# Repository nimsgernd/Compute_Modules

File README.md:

# Compute_Modules
I would like to design some compute modules for several processors that I would like more experience designing for. Not something I will be able to work on now but eventually.

Processors to support:
|   | Processor Name              |
| - | --------------------------- |
| 1 | AMD Xilinx Zynq UltraScale+ |
| 2 | AMD V2000                   |
| 3 | RP2350                      |
| 4 | STM32G491RET6               |
| 5 | STM32H75XXXXX - TBD         |

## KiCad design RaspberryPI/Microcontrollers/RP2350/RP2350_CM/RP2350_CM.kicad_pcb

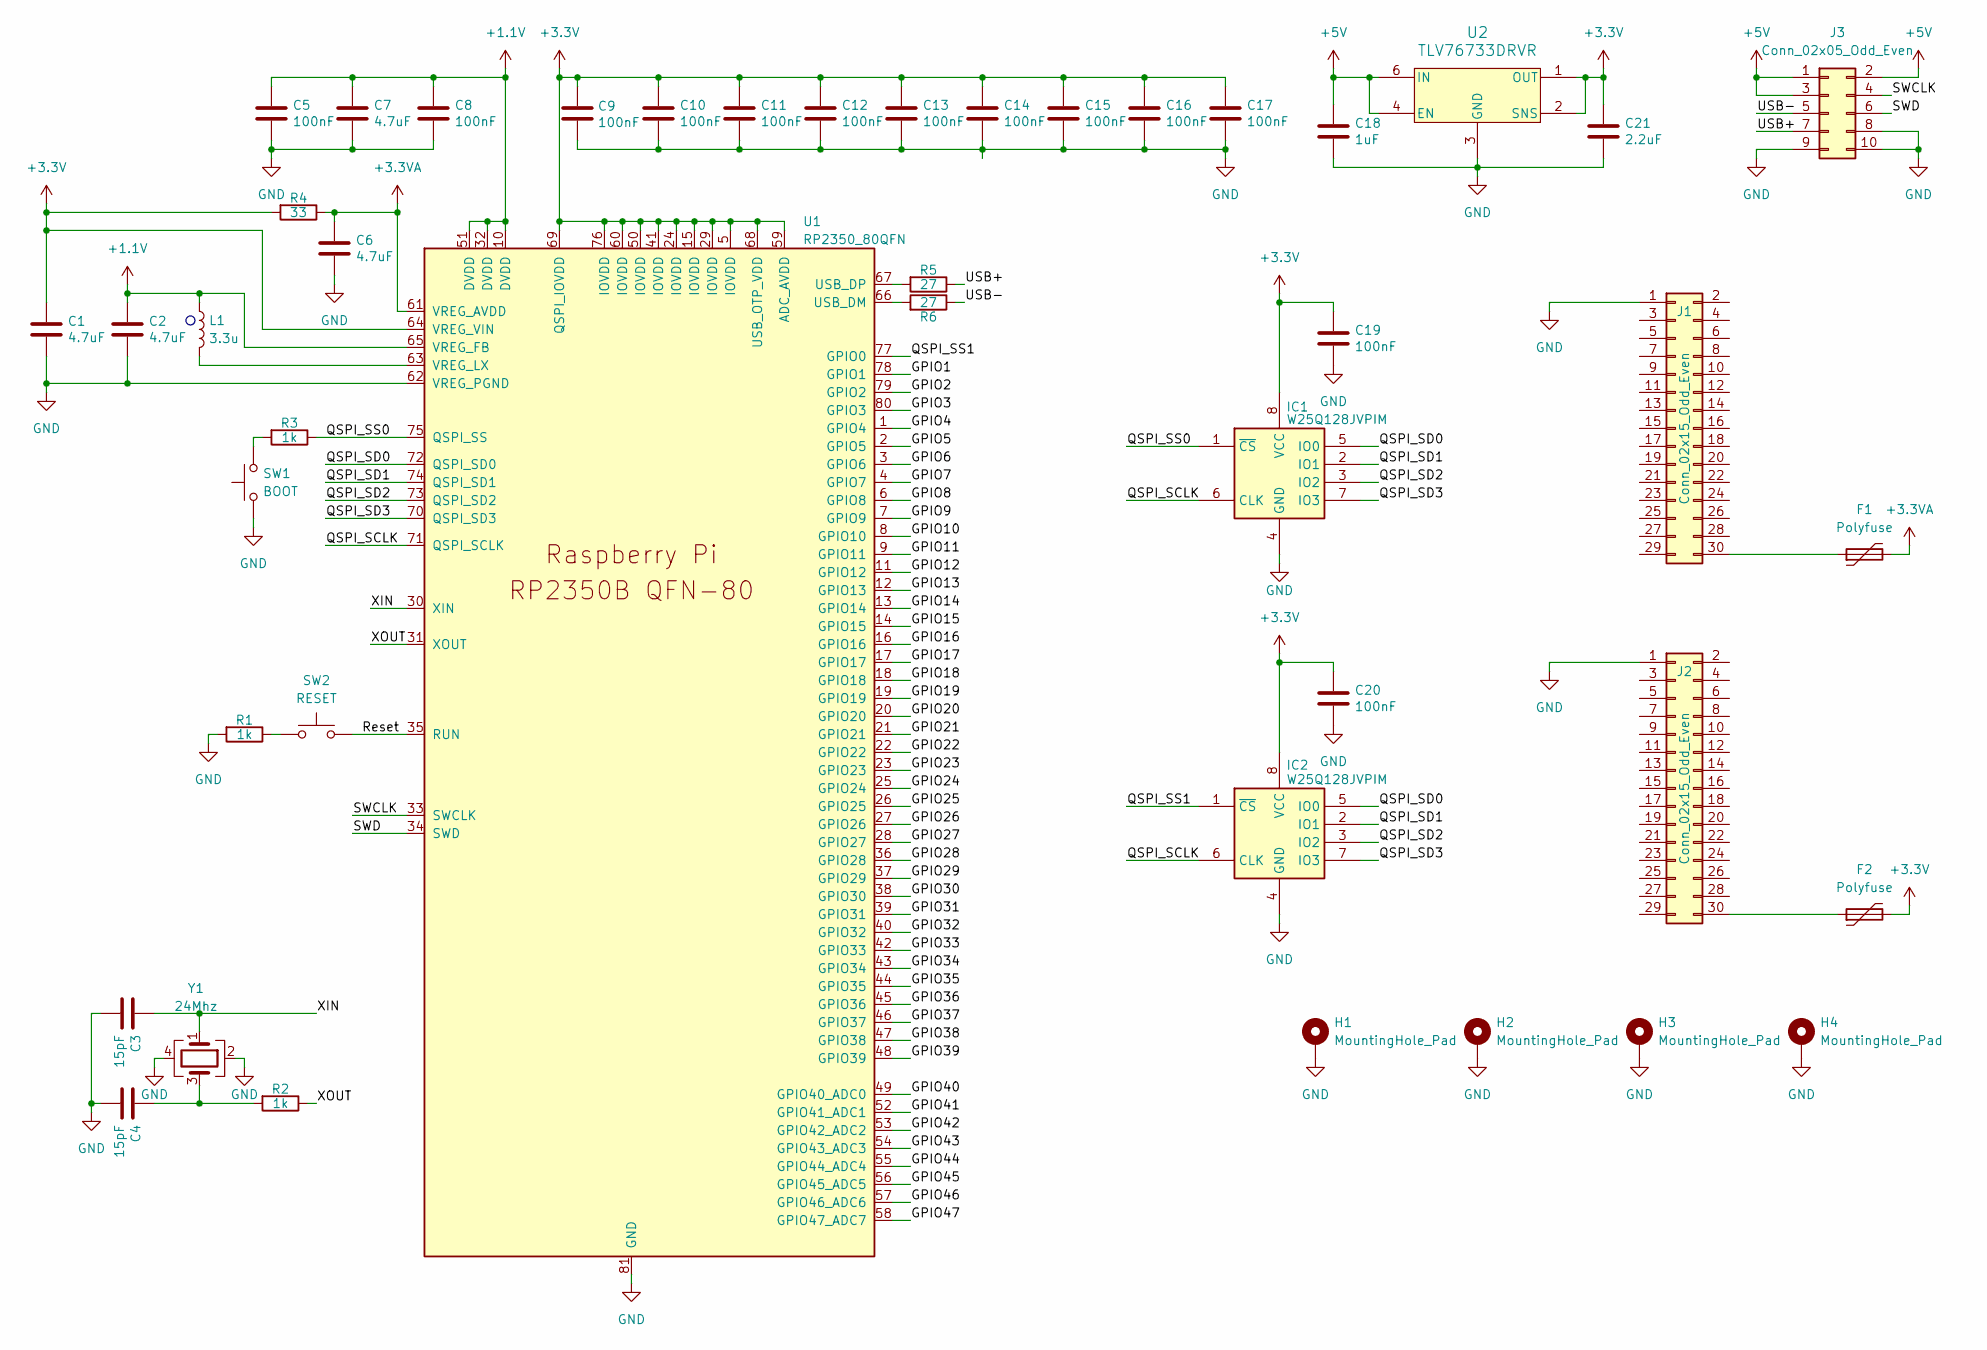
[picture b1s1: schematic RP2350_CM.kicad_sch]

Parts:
C1, C2, C6, C7: 4.7uF; C_0201_0603Metric
C3, C4: 15pF; C_0201_0603Metric
C5, C8, C9, C10, C11, C12, C13, C14, C15, C16, C17, C19, C20: 100nF; C_0201_0603Metric
C18: 1uF; C_0201_0603Metric
C21: 2.2uF; C_0201_0603Metric
F1, F2: Polyfuse; Fuse_0402_1005Metric
H1, H2, H3, H4: MountingHole_Pad; MountingHole_2.2mm_M2_Pad
IC1, IC2: W25Q128JVPIM; SON127P600X500X80-9N-D; Manufacturer_Part_Number W25Q128JVPIM; Mouser Part Number 454-W25Q128JVPIM
J1, J2: Conn_02x15_Odd_Even; Hirose_DF40C-30DP-0.4V_2x15-1MP_P0.4mm
J3: Conn_02x05_Odd_Even; CONN_DF40C-10DP-0.4V51_HIR
L1: 3.3u; L_pol_2016
R1, R2, R3: 1k; R_0201_0603Metric
R4: 33; R_0201_0603Metric
R5, R6: 27; R_0201_0603Metric
SW1: BOOT; B3U-1100P
SW2: RESET; B3U-1100P
U1: RP2350_80QFN; RP2350-QFN-80-1EP_10x10_P0.4mm_EP3.4x3.4mm_ThermalVias
U2: TLV76733DRVR; DRV0006A-MFG
Y1: 24Mhz; Crystal_SMD_1210-4Pin_1.2x1.0mm

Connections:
+1.1V: C2.1, C5.1, C7.1, C8.1, L1.1, U1.10 (DVDD), U1.32 (DVDD), U1.51 (DVDD), U1.65 (VREG_FB)
+3.3V: C1.1, C9.1, C10.1, C11.1, C12.1, C13.1, C14.1, C15.1, C16.1, C17.1, C19.1, C20.1, C21.1, F2.2, IC1.8 (VCC), IC2.8 (VCC), R4.2, U1.5 (IOVDD), U1.15 (IOVDD), U1.24 (IOVDD), U1.29 (IOVDD), U1.41 (IOVDD), U1.50 (IOVDD), U1.59 (ADC_AVDD), U1.60 (IOVDD), U1.64 (VREG_VIN), U1.68 (USB_OTP_VDD), U1.69 (QSPI_IOVDD), U1.76 (IOVDD), U2.1 (OUT), U2.2 (SNS)
+3.3VA: C6.1, F1.2, R4.1, U1.61 (VREG_AVDD)
+5V: C18.1, J3.1, J3.2, J3.3, U2.4 (EN), U2.6 (IN)
/GPIO1: U1.78 (GPIO1)
/GPIO2: U1.79 (GPIO2)
/GPIO3: U1.80 (GPIO3)
/GPIO4: U1.1 (GPIO4)
/GPIO5: U1.2 (GPIO5)
/GPIO6: U1.3 (GPIO6)
/GPIO7: U1.4 (GPIO7)
/GPIO8: U1.6 (GPIO8)
/GPIO9: U1.7 (GPIO9)
/GPIO10: U1.8 (GPIO10)
/GPIO11: U1.9 (GPIO11)
/GPIO12: U1.11 (GPIO12)
/GPIO13: U1.12 (GPIO13)
/GPIO14: U1.13 (GPIO14)
/GPIO15: U1.14 (GPIO15)
/GPIO16: U1.16 (GPIO16)
/GPIO17: U1.17 (GPIO17)
/GPIO18: U1.18 (GPIO18)
/GPIO19: U1.19 (GPIO19)
/GPIO20: U1.20 (GPIO20)
/GPIO21: U1.21 (GPIO21)
/GPIO22: U1.22 (GPIO22)
/GPIO23: U1.23 (GPIO23)
/GPIO24: U1.25 (GPIO24)
/GPIO25: U1.26 (GPIO25)
/GPIO26: U1.27 (GPIO26)
/GPIO27: U1.28 (GPIO27)
/GPIO28: U1.36 (GPIO28)
/GPIO29: U1.37 (GPIO29)
/GPIO30: U1.38 (GPIO30)
/GPIO31: U1.39 (GPIO31)
/GPIO32: U1.40 (GPIO32)
/GPIO33: U1.42 (GPIO33)
/GPIO34: U1.43 (GPIO34)
/GPIO35: U1.44 (GPIO35)
/GPIO36: U1.45 (GPIO36)
/GPIO37: U1.46 (GPIO37)
/GPIO38: U1.47 (GPIO38)
/GPIO39: U1.48 (GPIO39)
/GPIO40: U1.49 (GPIO40_ADC0)
/GPIO41: U1.52 (GPIO41_ADC1)
/GPIO42: U1.53 (GPIO42_ADC2)
/GPIO43: U1.54 (GPIO43_ADC3)
/GPIO44: U1.55 (GPIO44_ADC4)
/GPIO45: U1.56 (GPIO45_ADC5)
/GPIO46: U1.57 (GPIO46_ADC6)
/GPIO47: U1.58 (GPIO47_ADC7)
/QSPI_SCLK: IC1.6 (CLK), IC2.6 (CLK), U1.71 (QSPI_SCLK)
/QSPI_SD0: IC1.5 (IO0), IC2.5 (IO0), U1.72 (QSPI_SD0)
/QSPI_SD1: IC1.2 (IO1), IC2.2 (IO1), U1.74 (QSPI_SD1)
/QSPI_SD2: IC1.3 (IO2), IC2.3 (IO2), U1.73 (QSPI_SD2)
/QSPI_SD3: IC1.7 (IO3), IC2.7 (IO3), U1.70 (QSPI_SD3)
/QSPI_SS0: IC1.1 (~CS), R3.1, U1.75 (QSPI_SS)
/QSPI_SS1: IC2.1 (~CS), U1.77 (GPIO0)
/Reset: SW2.2, U1.35 (RUN)
/SWCLK: J3.4, U1.33 (SWCLK)
/SWD: J3.6, U1.34 (SWD)
/USB+: J3.7, R5.1
/USB-: J3.5, R6.1
/XIN: C3.1, U1.30 (XIN), Y1.1
/XOUT: R2.1, U1.31 (XOUT)
GND: C1.2, C2.2, C3.2, C4.2, C5.2, C6.2, C7.2, C8.2, C9.2, C10.2, C11.2, C12.2, C13.2, C14.2, C15.2, C16.2, C17.2, C18.2, C19.2, C20.2, C21.2, H1.1, H2.1, H3.1, H4.1, IC1.4 (GND), IC1.9 (EP), IC2.4 (GND), IC2.9 (EP), J1.1, J2.1, J3.8, J3.9, J3.10, R1.2, SW1.1, U1.62 (VREG_PGND), U1.81 (GND), U2.3 (GND), U2.5 (GND), U2.7 (Thermal_Pad), Y1.2, Y1.4
unnamed: C4.1, R2.2, Y1.3
unnamed: F1.1, J1.30
unnamed: F2.1, J2.30
unnamed: R1.1, SW2.1
unnamed: R3.2, SW1.2
unnamed: R6.2, U1.66 (USB_DM)
unnamed: R5.2, U1.67 (USB_DP)
unnamed: L1.2, U1.63 (VREG_LX)

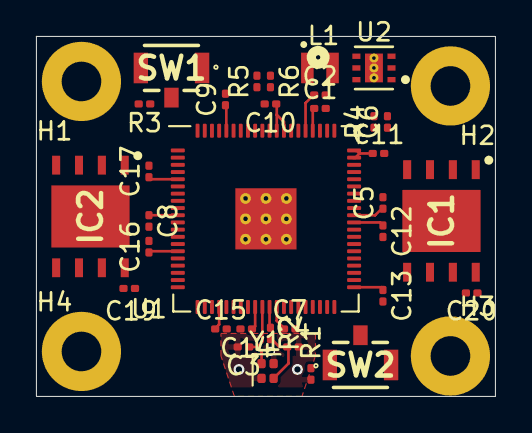
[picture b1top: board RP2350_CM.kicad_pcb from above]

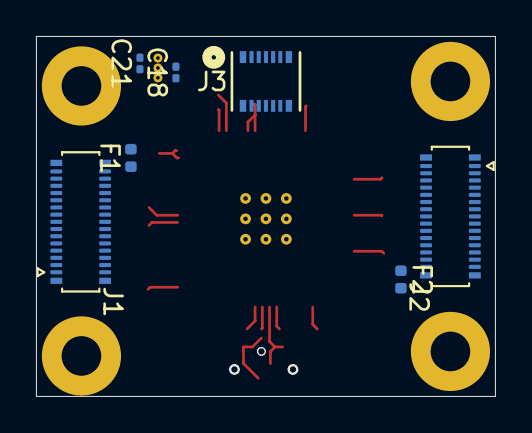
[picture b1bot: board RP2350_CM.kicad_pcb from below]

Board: 4 copper layers, 25.5 x 20.0 mm, 44 parts (7 on the bottom side), 27 nets.

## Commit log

2025-10-16 Adding RP2350 Compute Module
    I was working on this for a little bit but I figured I should add this.
2025-11-08 Add new processor entries to README
2025-11-08 Add README for STM32G491 Compute Module
2025-11-08 Add placeholder for STM32H7 Compute Module README
2025-11-08 Generated STM Compute Module Software
    - Added occilators for HSE and LSE
    - Configured both projects for the expected hardware
    - Both projects are configured with:
    - Azure RTOS
    - ThreadX
    - USBX
